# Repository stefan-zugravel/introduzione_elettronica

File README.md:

# Corso introduttivo "Flusso di progettazione elettronica"
Il corso prevede 4 ore di lezione frontale e diversi laboratori da svolgere in autonomia.
Per scaricare sulla propria workstation tutto il materiale:
`git clone https://github.com/stefan-zugravel/introduzione_elettronica.git`
oppure:
`git clone git@github.com:stefan-zugravel/introduzione_elettronica.git`
in base a proprio metodo di autenticazione preferito (consiglio chiave ssh)
**Se non avete mai uasto GIT vi consiglio di guardare uno di due video prima del corso**
- [video 1](https://www.youtube.com/watch?v=8JJ101D3knE)
- [video 2](https://www.youtube.com/watch?v=tRZGeaHPoaw)
***
## Lezione online sincrona
Dato il limitato tempo a disposizione la lezione sicrona si dovrà concentrare maggiormente sull'aspetto teorico e su ebventuali consigli pratici. Cercheremo comunque di vedere assieme, per i due tool più importanti (KiCAD e VIVADO), come creare un nuoo progetto e quali sono le funzioni principali del tool.
- Istruzioni per accedere ai laboratori con le consegne e le soluzioni (15 min) 
- Introduzione pcb con slides (45 min circa)
- KiCAD, aggiungere componenti, come funziona il tool e qualche accorgimento (45 min)
- Informazioni più generali sul workflow, BOM, produzione, materiali ecc (15 min)
- Pausa 10 min
- VHDL e FPGA introduzione con slides (60 min)
- VIVADO, introduzione al tool e strumenti principali (fino a termine lezione)
***
## Laboratori
### Lab 0 - Laboratorio introduttivo su GIT
**Consegna:** Crea una nuova *repo* su GitHub con un gitignore, una licenza e un README. Fai il *push* di un *commit*, crea una o più nuove *branch* e fanne il merge.
Per prendere dimestichezza con il tool consiglio di creare una *repo* diversa per ogni nuovo laboratorio.
### Lab 1 - Tastierino in KiCAD
**Consegna:** In KiCAD realizza lo schematico, il layout e i file di produzione per un tastierino da 16 pulsanti. Questo laboratorio verrà svolto durante la lezione come introduzione al software.
### Lab 2 - Skew e length tuning in KiCAD
**Consegna:** Crea un nuovo progetto, importa due coppie di connettori coassiali a due poli (esempio: LEMO-EPG.00.302.NLN) e prendi dimestichezza con i tool di de-skewing e length tuning per le coppie differenziali e single ended. Sulle slides puoi trovare i link a due brevi video tutorial.
### Lab 3 - Amperometro in KiCAD
**Consegna:** Progetta (diagramma a blocchi, schematico, layout e file di produzione) un amperometro con le seguenti specifiche:
- 8 canali in ingresso
- Range di misurazione da 5 uA a 700 uA
- Risoluzione 16 bit
- Frequenza di campionamento di almeno 100 Sps
- FEE isolato galvanicamnete dalla parte digitale
- Filtro passa basso prima della digitalizzazione di 20 KHz -3 dB
- Invio dei dati ad un PC tramite ethernet TCP-IP

**Domande da porsi:**
- Devo usare un microcontrollore o un FPGA? Perché? Quali sono i benefit di uno e dell'altro?
- Come faccio a portare il power al FEE mantenendo l'isolazione galvanica?
- Cosa uso per implementare il protocollo ethernet TCP-IP in maniera semplice, veloce ed economica?
- Come posso misurare delle correnti così piccole? Che componenti devo usare?

**Consiglio:** 
- Controllate questo [modulo](https://docs.wiznet.io/Product/Chip/MCU/W55RP20/w55rp20-evb-pico), può esservi utile?

**Raccomandazioni:**
- Cercate di usare il meno possibile le soluzioni. Soprattutto per questo laboratorio. La parte più difficile del design molte volte è proprio all'inizio, scegliere l'architettura, il tipo di circuito da usare e su quali componenti fare affidamento. Ho volutamente omesso dai consigli tutti gli altri componenti da usare. Fate le vostre scelte e poi confrontatevi con la soluzione proposta (che non è detto essere la migliore).

### Lab 4 - FPGA e KiCAD
**Consegna:** Importa un FPGA a scelta in KiCAD, collega il power e qualche linea dati e prova a farne il layout. Questo laboratorio è il più _"difficile"_ in quanto le tolleranze in gioco sono generalmente piccole e la soluizone mostra solo un esempio di un layout finito e non un effettivo punto di arrivo del laboratorio. Sulle slides puoi trovare i link a due brevi video tutorial. Prendi il tempo necessario e **leggi la documentazione** dell'FPGA che hai scelto.
### Lab 5 - Introduzione a LTspice
**Consegna:** Con LTspice disegna lo schematico ed esegui la simulazione dei seguenti circuiti analogici:
- Un semplice partitore resistivo (simulazione .op e un .dc sweep)
- Amplificatore operazionale in configurazione non invertente (simulazione .ac e .tran)
- Amplificatore operazionale in configurazione invertente (simulazione .ac e .tran)
- Caratterizzazione di un MOSFET (che tipo di simulazione conviene usare?)
- Amplificatore operazionale importando una libreria esterna (il file .LIB è presente nella cartella del lab5)
- Amplificatore operazionale con feedback capacitivo (simulazione .ac e .tran)

**Consiglio di ripetere tutti i circuiti fatti su LTspice usando il simulatore integrato in KiCAD (ngspice).**

### Lab 6
**Consegna:** Usando VIVADO scrivi in VHDL i moduli per un inverter, per le porte logiche AND, OR, NAND, NOR, XOR, XNOR e il modulo per un multiplexer (questo può essere fatto in più varianti). Questo laboratorio verrà svolto durante la lezione come introduzione al software, vedremo inoltre il concetto di testbench, di sintesi e implementazione, il file di constraints e la generazione del bitfile.

### Lab 7
**Consegna:** Scivi in VHDL un BCD (Contatore Decimale condificato in Binario):
- Come posso variare la sua velocità di aggiornamento?
- Quanto lento lo posso far andare? E invece quanto veloce?
- Come posso configure la sua velocità nel modo più efficiente possibile?

### Lab 8
**Consegna:** Scrivi in VHDL una macchina a stati per il controllo dei semafori in un incrocio stradale. La parte importante di questo laboratorio è tutta la sintassi della macchina a stati finiti (FSM). In questo caso consiglio di guardare le soluzioni, prendere spunto e aggiungere uno stato di _allarme_ e uno di _inizializzazione_.

### Lab 9
**Consegna:** Usa il block diagram di VIVADO per implementare un FIR passa basso digitale usando due DDS compiler, un modulo di somma e una ILA. Il modulo del FIR puoi prenderlo dalla soluzioni. Cerca però di comprenderne il funzionamento. Consiglio di provare a modificarlo aumentando il numero di taps.

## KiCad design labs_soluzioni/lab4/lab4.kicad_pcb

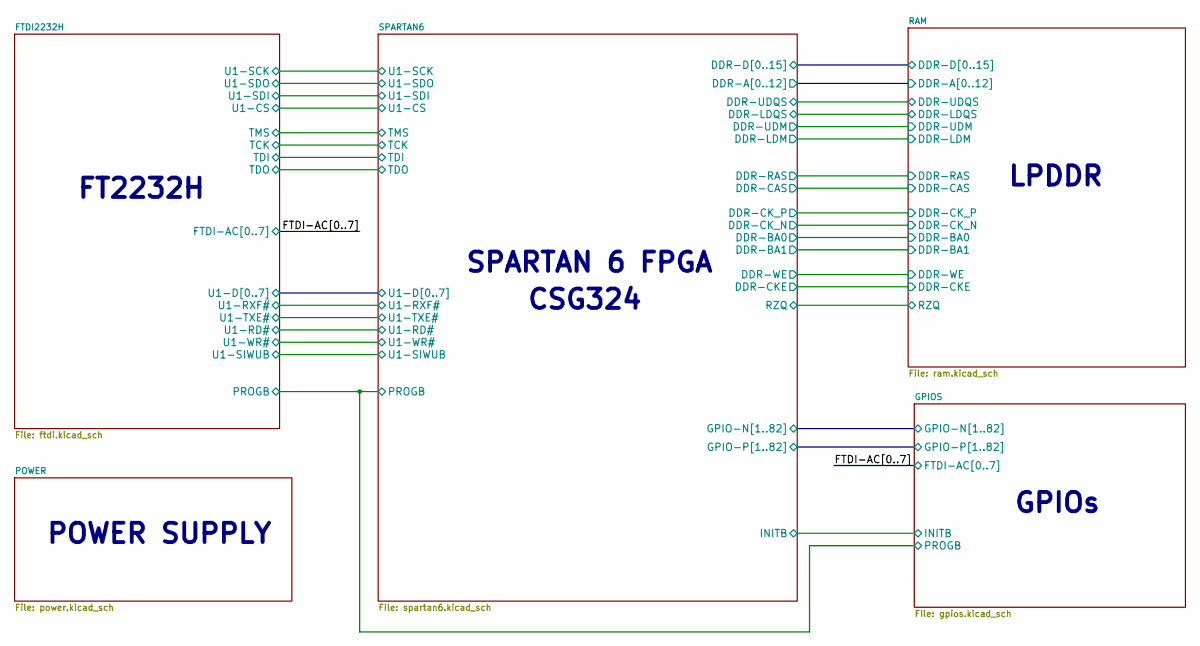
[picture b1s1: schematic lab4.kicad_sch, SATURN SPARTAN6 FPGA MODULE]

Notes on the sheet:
FT2232H
SPARTAN 6 FPGA
CSG324
GPIOs
LPDDR
POWER SUPPLY

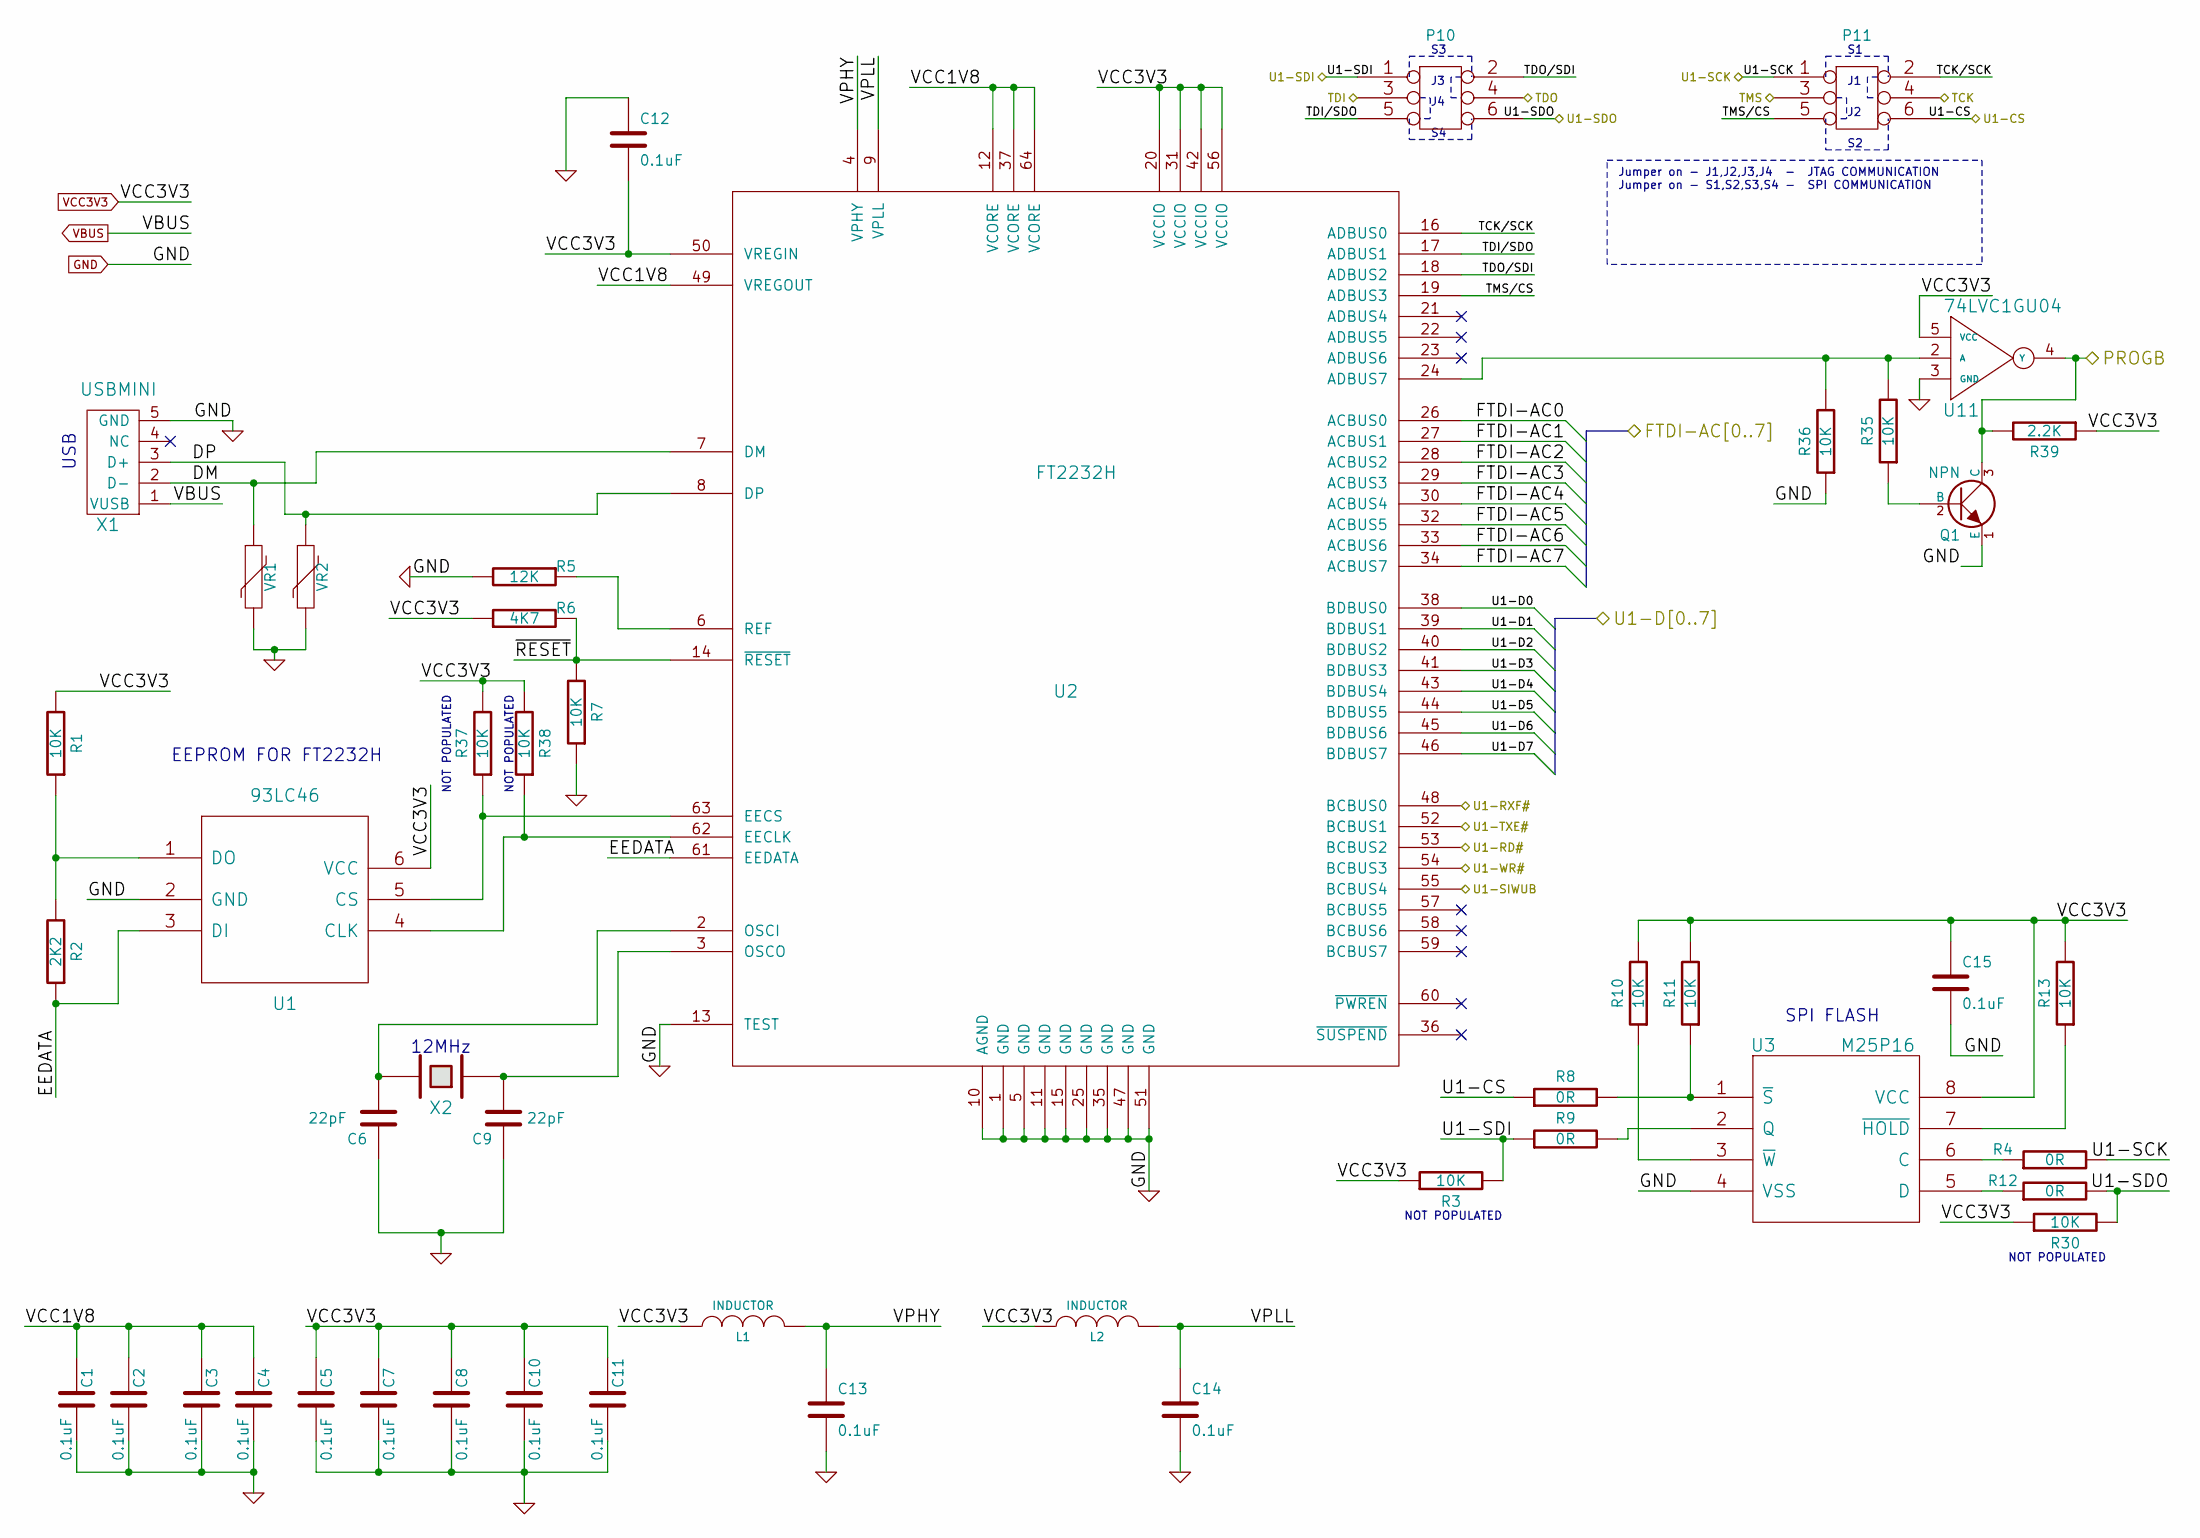
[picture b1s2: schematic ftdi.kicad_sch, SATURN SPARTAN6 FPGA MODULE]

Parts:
C1, C2, C3, C4, C5, C7, C8, C10, C11, C12, C13, C14, C15: 0.1uF
C6, C9: 22pF
L1, L2: INDUCTOR
P10, P11: CONN_3X2
Q1: NPN
R1, R3, R7, R10, R11, R13, R30, R35, R36, R37, R38: 10K
R2: 2K2
R4, R8, R9, R12: 0R
R5: 12K
R6: 4K7
R39: 2.2K
U1: 93LC46
U2: FT2232H
U3: M25P16
U11: 74LVC1GU04
VR1, VR2: VR
X1: USBMINI
X2: CRYSTAL

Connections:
/FTDI2232H/DM: U2.7 (DM), VR1.1, X1.2 (D-)
/FTDI2232H/DP: U2.8 (DP), VR2.1, X1.3 (D+)
/FTDI2232H/EEDATA: R2.1, U1.3 (DI), U2.61 (EEDATA)
/FTDI2232H/FTDI-AC0: U2.26 (ACBUS0); also elsewhere on the board
/FTDI2232H/FTDI-AC1: U2.27 (ACBUS1); also elsewhere on the board
/FTDI2232H/FTDI-AC2: U2.28 (ACBUS2); also elsewhere on the board
/FTDI2232H/FTDI-AC3: U2.29 (ACBUS3); also elsewhere on the board
/FTDI2232H/FTDI-AC4: U2.30 (ACBUS4); also elsewhere on the board
/FTDI2232H/FTDI-AC5: U2.32 (ACBUS5); also elsewhere on the board
/FTDI2232H/FTDI-AC6: U2.33 (ACBUS6); also elsewhere on the board
/FTDI2232H/FTDI-AC7: U2.34 (ACBUS7); also elsewhere on the board
/FTDI2232H/PROGB: Q1.3 (C), R39.2, U11.4 (Y); also elsewhere on the board
/FTDI2232H/TCK: P11.4; also elsewhere on the board
/FTDI2232H/TCK/SCK: P11.2, U2.16 (ADBUS0)
/FTDI2232H/TDI: P10.3; also elsewhere on the board
/FTDI2232H/TDI/SDO: P10.5, U2.17 (ADBUS1)
/FTDI2232H/TDO: P10.4; also elsewhere on the board
/FTDI2232H/TDO/SDI: P10.2, U2.18 (ADBUS2)
/FTDI2232H/TMS: P11.3; also elsewhere on the board
/FTDI2232H/TMS/CS: P11.5, U2.19 (ADBUS3)
/FTDI2232H/U1-CS: P11.6, R8.1; also elsewhere on the board
/FTDI2232H/U1-D0: U2.38 (BDBUS0); also elsewhere on the board
/FTDI2232H/U1-D1: U2.39 (BDBUS1); also elsewhere on the board
/FTDI2232H/U1-D2: U2.40 (BDBUS2); also elsewhere on the board
/FTDI2232H/U1-D3: U2.41 (BDBUS3); also elsewhere on the board
/FTDI2232H/U1-D4: U2.43 (BDBUS4); also elsewhere on the board
/FTDI2232H/U1-D5: U2.44 (BDBUS5); also elsewhere on the board
/FTDI2232H/U1-D6: U2.45 (BDBUS6); also elsewhere on the board
/FTDI2232H/U1-D7: U2.46 (BDBUS7); also elsewhere on the board
/FTDI2232H/U1-RD#: U2.53 (BCBUS2); also elsewhere on the board
/FTDI2232H/U1-RXF#: U2.48 (BCBUS0); also elsewhere on the board
/FTDI2232H/U1-SCK: P11.1, R4.2; also elsewhere on the board
/FTDI2232H/U1-SDI: P10.1, R3.2, R9.1; also elsewhere on the board
/FTDI2232H/U1-SDO: P10.6, R12.2, R30.2; also elsewhere on the board
/FTDI2232H/U1-SIWUB: U2.55 (BCBUS4); also elsewhere on the board
/FTDI2232H/U1-TXE#: U2.52 (BCBUS1); also elsewhere on the board
/FTDI2232H/U1-WR#: U2.54 (BCBUS3); also elsewhere on the board
/FTDI2232H/VCC1V8: C1.1, C2.1, C3.1, C4.1, U2.12 (VCORE), U2.37 (VCORE), U2.49 (VREGOUT), U2.64 (VCORE)
/FTDI2232H/VPHY: C13.1, L1.2, U2.4 (VPHY)
/FTDI2232H/VPLL: C14.1, L2.2, U2.9 (VPLL)
/FTDI2232H/~RESET: R6.2, R7.2, U2.14 (~RESET)
GND: C1.2, C2.2, C3.2, C4.2, C5.2, C6.1, C7.2, C8.2, C9.1, C10.2, C11.2, C12.1, C13.2, C14.2, C15.2, Q1.1 (E), R5.2, R7.1, R36.1, U1.2 (GND), U2.1 (GND), U2.5 (GND), U2.10 (AGND), U2.11 (GND), U2.13 (TEST), U2.15 (GND), U2.25 (GND), U2.35 (GND), U2.47 (GND), U2.51 (GND), U3.4 (VSS), U11.3 (GND), VR1.2, VR2.2, X1.0, X1.5 (GND); also elsewhere on the board
unnamed: R13.1, U3.7 (~HOLD)
unnamed: R9.2, U3.2 (Q)
unnamed: R12.1, U3.5 (D)
unnamed: R8.2, R11.1, U3.1 (~S)
unnamed: R10.1, U3.3 (~W)
unnamed: R4.1, U3.6 (C)
unnamed: R35.2, R36.2, U2.24 (ADBUS7), U11.2 (A)
unnamed: C9.2, U2.3 (OSCO), X2.1
unnamed: R37.1, U1.5 (CS), U2.63 (EECS)
unnamed: R1.1, R2.2, U1.1 (DO)
unnamed: C6.2, U2.2 (OSCI), X2.2
unnamed: Q1.2 (B), R35.1
unnamed: R38.1, U1.4 (CLK), U2.62 (EECLK)
unnamed: R5.1, U2.6 (REF)
VBUS: X1.1 (VUSB); also elsewhere on the board
VCC3V3: C5.1, C7.1, C8.1, C10.1, C11.1, C12.2, C15.1, L1.1, L2.1, R1.2, R3.1, R6.1, R10.2, R11.2, R13.2, R30.1, R37.2, R38.2, R39.1, U1.6 (VCC), U2.20 (VCCIO), U2.31 (VCCIO), U2.42 (VCCIO), U2.50 (VREGIN), U2.56 (VCCIO), U3.8 (VCC), U11.5 (VCC); also elsewhere on the board

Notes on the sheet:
NOT POPULATED
12MHz
EEPROM FOR FT2232H
SPI FLASH
USB
Jumper on - J1,J2,J3,J4 - JTAG COMMUNICATION Jumper on - S1,S2,S3,S4 - SPI COMMUNICATION

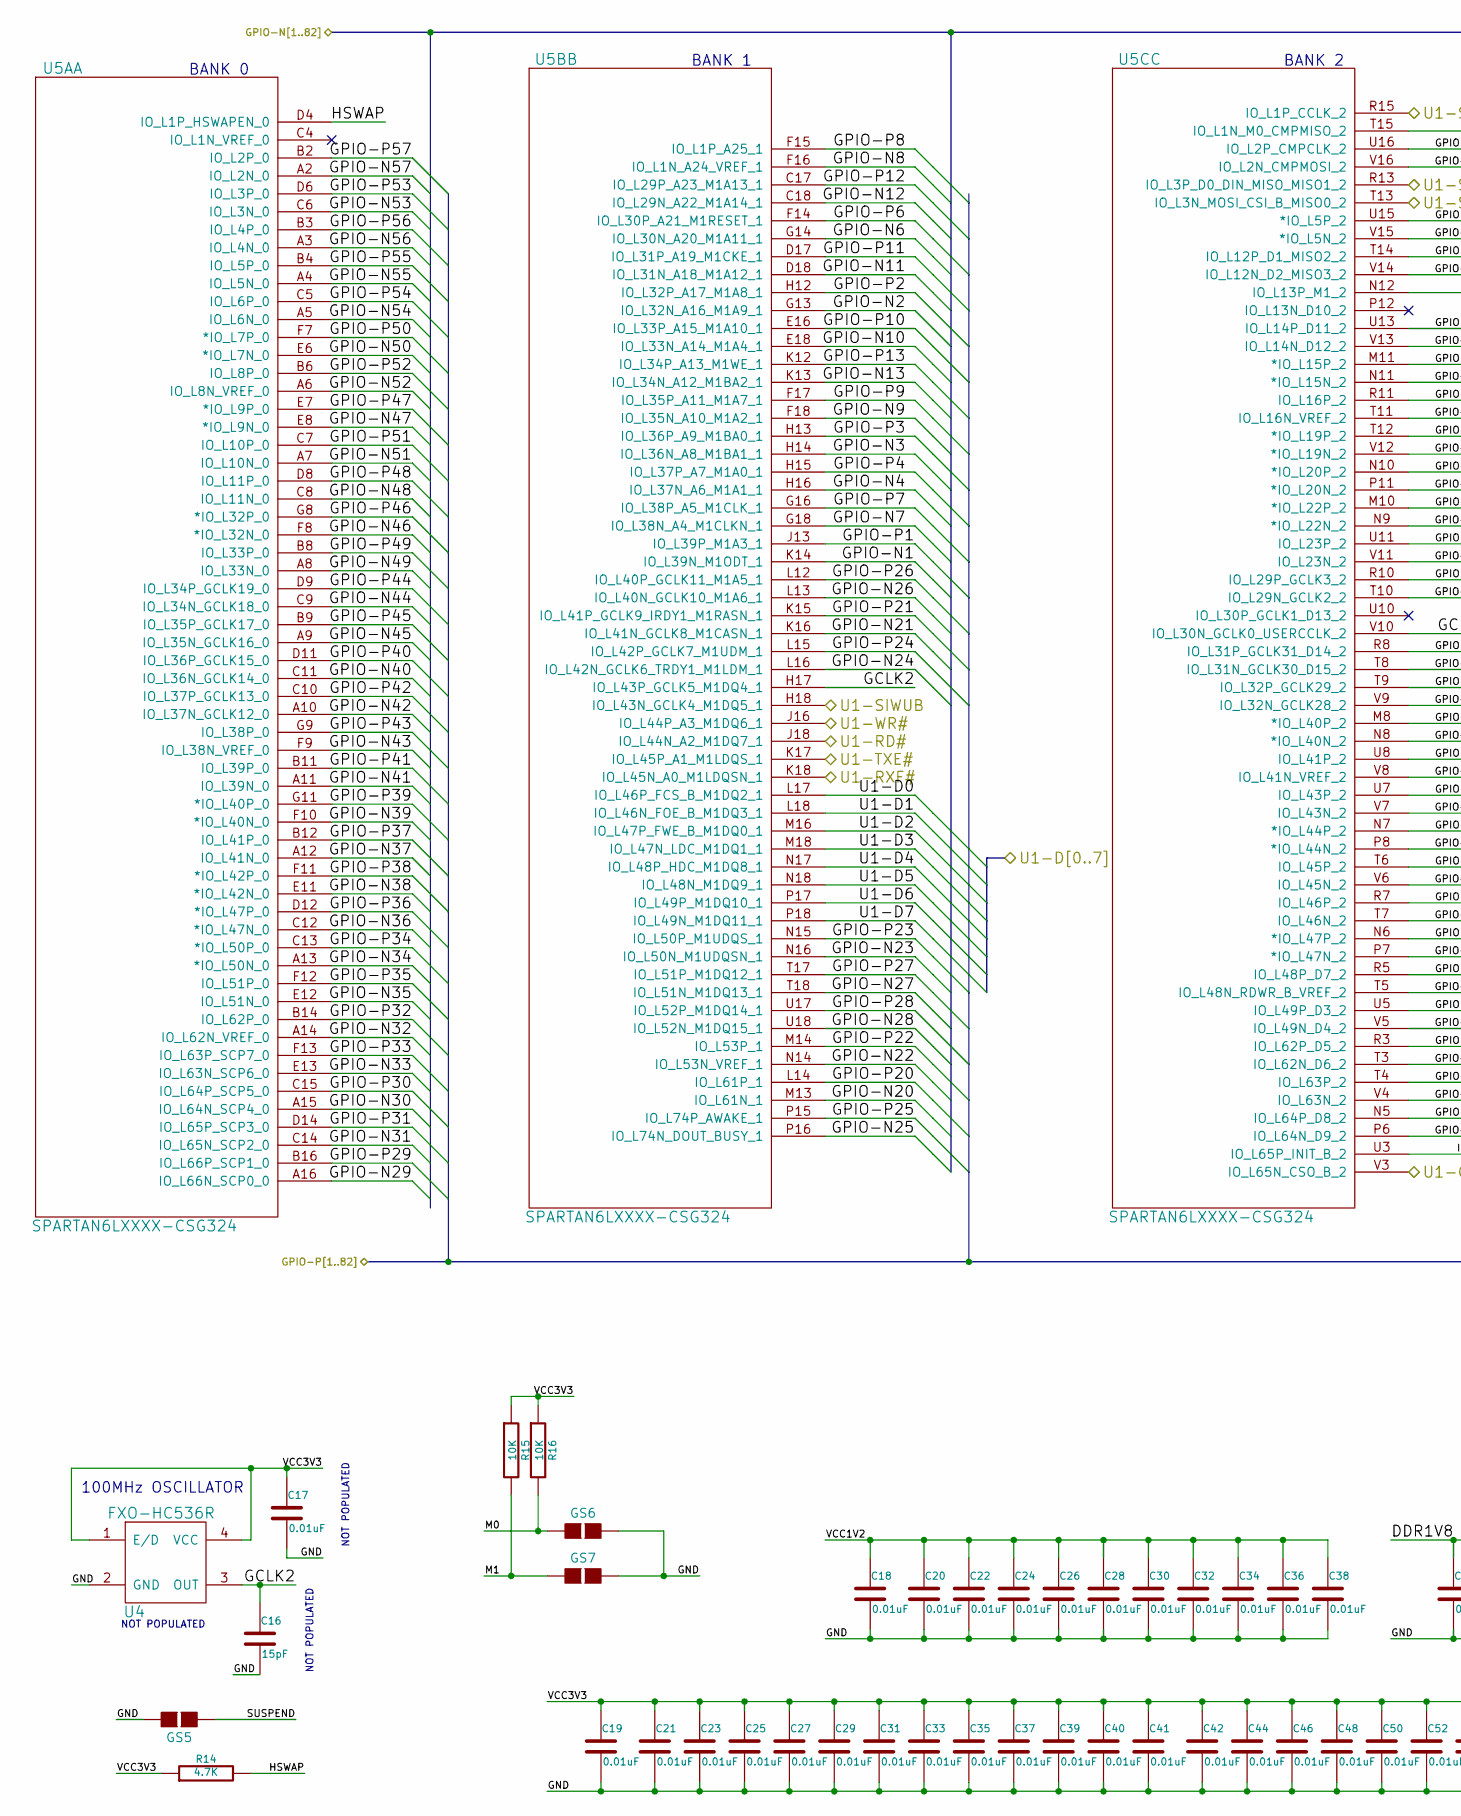
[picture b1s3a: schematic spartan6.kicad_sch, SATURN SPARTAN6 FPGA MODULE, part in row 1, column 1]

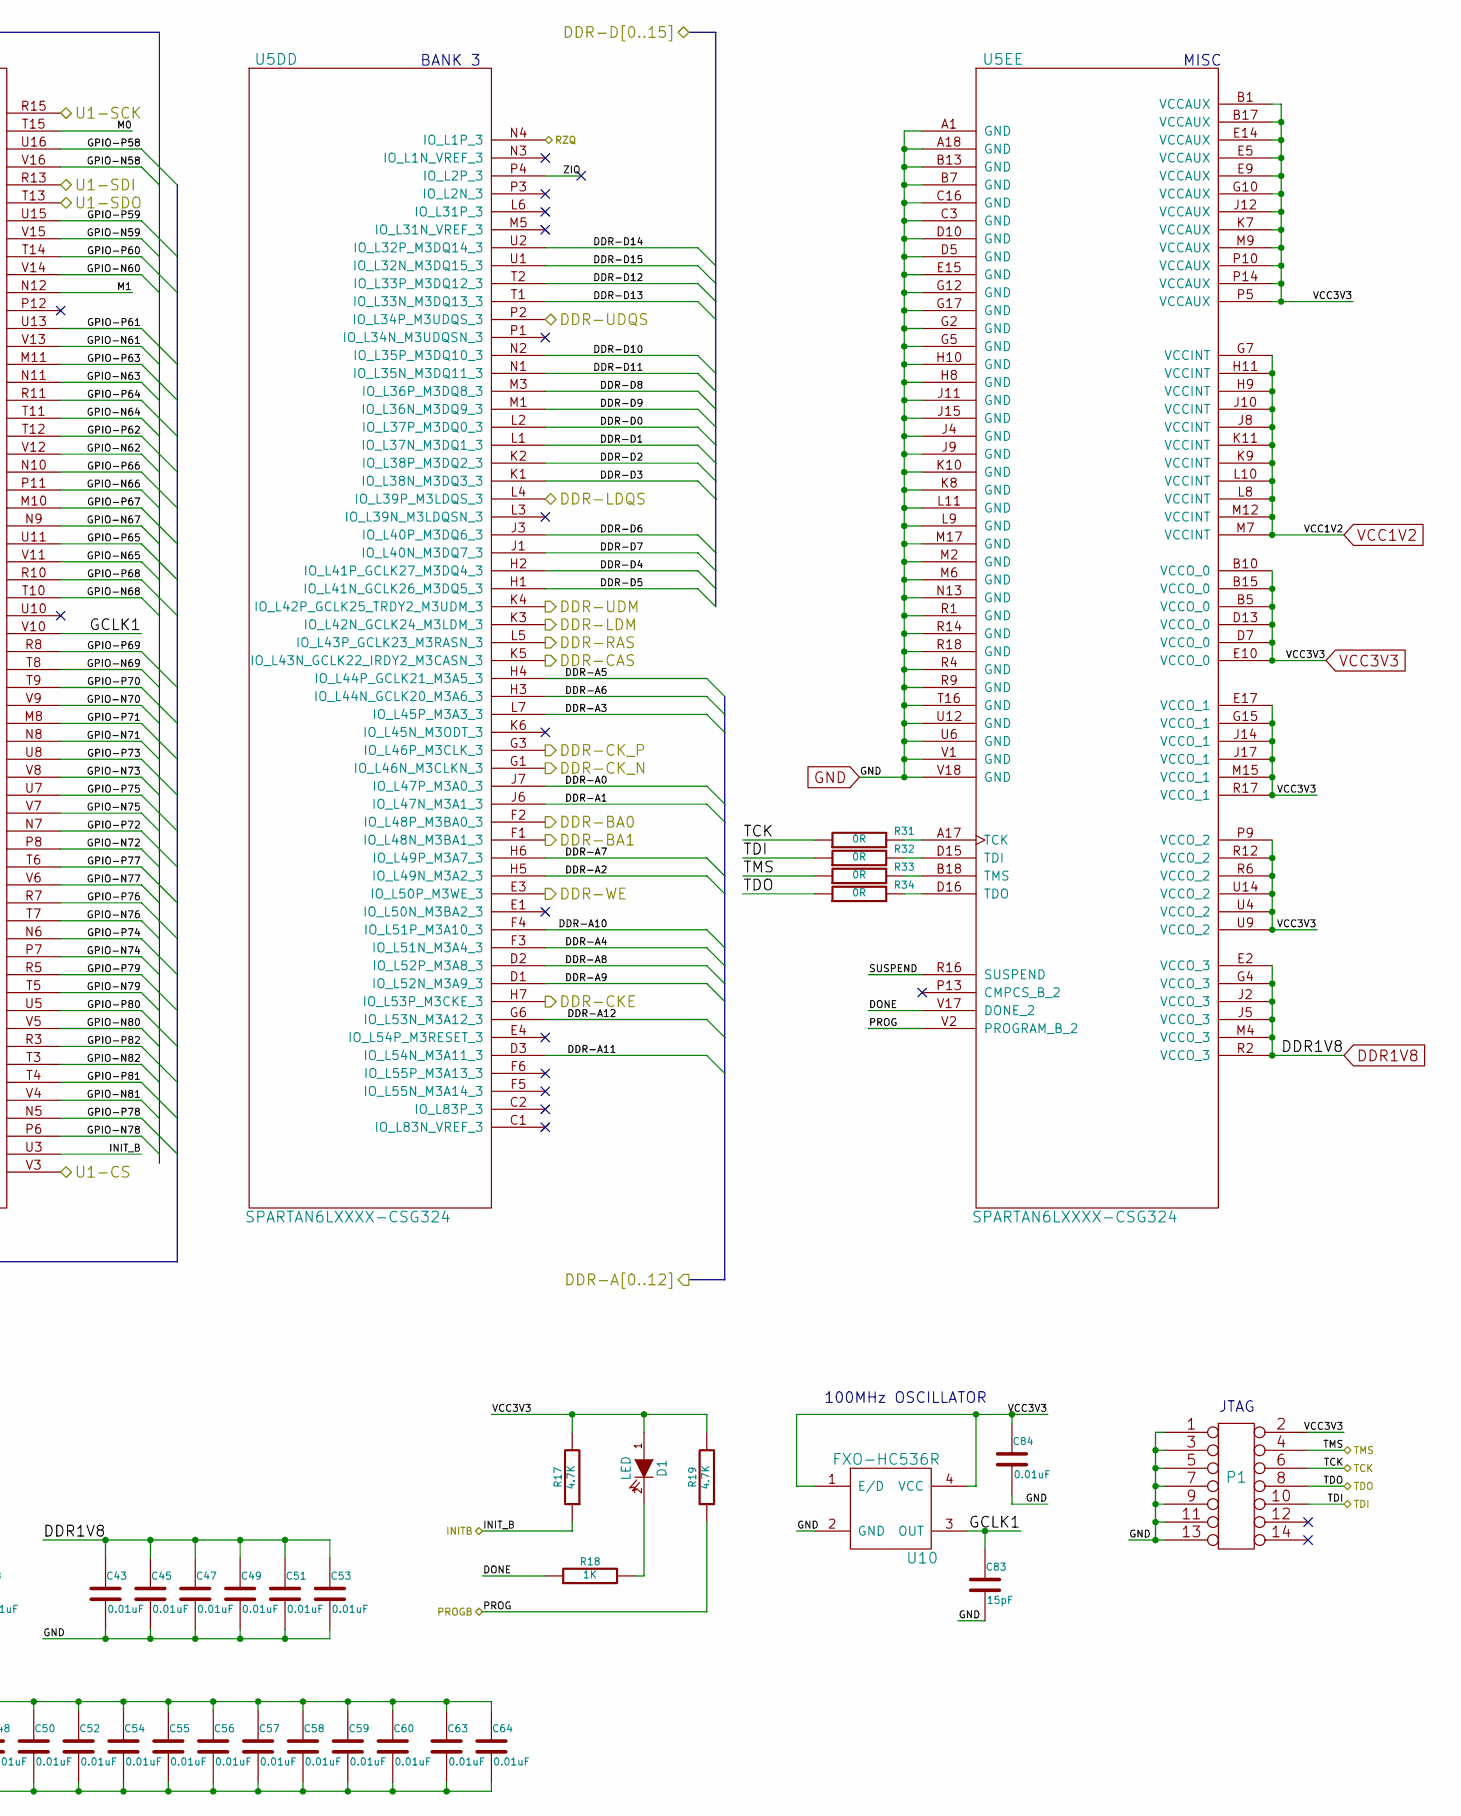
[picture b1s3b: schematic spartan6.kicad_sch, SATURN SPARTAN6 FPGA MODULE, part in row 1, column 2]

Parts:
C16, C83: 15pF
C17, C18, C19, C20, C21, C22, C23, C24, C25, C26, C27, C28, C29, C30, C31, C32, C33, C34, C35, C36, C37, C38, C39, C40, C41, C42, C43, C44, C45, C46, C47, C48, C49, C50, C51, C52, C53, C54, C55, C56, C57, C58, C59, C60, C63, C64, C84: 0.01uF
D1: LED
GS5, GS6, GS7: GS2
P1: CONN_7X2
R14, R17, R19: 4.7K
R15, R16: 10K
R18: 1K
R31, R32, R33, R34: 0R
U4, U10: FXO-HC536R
U5A, U5B, U5C, U5D, U5E: SPARTAN6LXXXX-CSG324

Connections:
/FTDI2232H/PROGB: R19.1, U5E.V2 (PROGRAM_B_2); also elsewhere on the board
/FTDI2232H/TCK: P1.6, R31.1; also elsewhere on the board
/FTDI2232H/TDI: P1.10, R32.1; also elsewhere on the board
/FTDI2232H/TDO: P1.8, R34.1; also elsewhere on the board
/FTDI2232H/TMS: P1.4, R33.1; also elsewhere on the board
/GPIOS/INITB: R17.1, U5C.U3 (IO_L65P_INIT_B_2); also elsewhere on the board
/SPARTAN6/DONE: R18.1, U5E.V17 (DONE_2); also elsewhere on the board
/SPARTAN6/GCLK1: C83.1, U5C.V10 (IO_L30N_GCLK0_USERCCLK_2), U10.3 (OUT); also elsewhere on the board
/SPARTAN6/GCLK2: C16.1, U4.3 (OUT), U5B.H17 (IO_L43P_GCLK5_M1DQ4_1); also elsewhere on the board
/SPARTAN6/HSWAP: R14.2, U5A.D4 (IO_L1P_HSWAPEN_0); also elsewhere on the board
/SPARTAN6/M0: GS6.1 (G1), R16.2, U5C.T15 (IO_L1N_M0_CMPMISO_2); also elsewhere on the board
/SPARTAN6/M1: GS7.1 (G1), R15.2, U5C.N12 (IO_L13P_M1_2); also elsewhere on the board
/SPARTAN6/SUSPEND: GS5.1 (G1), U5E.R16 (SUSPEND); also elsewhere on the board
DDR1V8: C43.1, C45.1, C47.1, C49.1, C51.1, C53.1, U5E.E2 (VCCO_3), U5E.G4 (VCCO_3), U5E.J2 (VCCO_3), U5E.J5 (VCCO_3), U5E.M4 (VCCO_3), U5E.R2 (VCCO_3); also elsewhere on the board
GND: C16.2, C17.2, C18.2, C19.2, C20.2, C21.2, C22.2, C23.2, C24.2, C25.2, C26.2, C27.2, C28.2, C29.2, C30.2, C31.2, C32.2, C33.2, C34.2, C35.2, C36.2, C37.2, C38.2, C39.2, C40.2, C41.2, C42.2, C43.2, C44.2, C45.2, C46.2, C47.2, C48.2, C49.2, C50.2, C51.2, C52.2, C53.2, C54.2, C55.2, C56.2, C57.2, C58.2, C59.2, C60.2, C63.2, C64.2, C83.2, C84.2, GS5.2 (G2), GS6.2 (G2), GS7.2 (G2), P1.1, P1.3, P1.5, P1.7, P1.9, P1.11, P1.13, U4.2 (GND), U5E.A1 (GND), U5E.A18 (GND), U5E.B7 (GND), U5E.B13 (GND), U5E.C3 (GND), U5E.C16 (GND), U5E.D5 (GND), U5E.D10 (GND), U5E.E15 (GND), U5E.G2 (GND), U5E.G5 (GND), U5E.G12 (GND), U5E.G17 (GND), U5E.H8 (GND), U5E.H10 (GND), U5E.J4 (GND), U5E.J9 (GND), U5E.J11 (GND), U5E.J15 (GND), U5E.K8 (GND), U5E.K10 (GND), U5E.L9 (GND), U5E.L11 (GND), U5E.M2 (GND), U5E.M6 (GND), U5E.M17 (GND), U5E.N13 (GND), U5E.R1 (GND), U5E.R4 (GND), U5E.R9 (GND), U5E.R14 (GND), U5E.R18 (GND), U5E.T16 (GND), U5E.U6 (GND), U5E.U12 (GND), U5E.V1 (GND), U5E.V18 (GND), U10.2 (GND); also elsewhere on the board
unnamed 257: R31.2, U5E.A17 (TCK); also elsewhere on the board
unnamed 258: R34.2, U5E.D16 (TDO); also elsewhere on the board
unnamed 259: R32.2, U5E.D15 (TDI); also elsewhere on the board
unnamed 260: R33.2, U5E.B18 (TMS); also elsewhere on the board
unnamed: D1.2 (K), R18.2
VCC1V2: C18.1, C20.1, C22.1, C24.1, C26.1, C28.1, C30.1, C32.1, C34.1, C36.1, C38.1, U5E.G7 (VCCINT), U5E.H9 (VCCINT), U5E.H11 (VCCINT), U5E.J8 (VCCINT), U5E.J10 (VCCINT), U5E.K9 (VCCINT), U5E.K11 (VCCINT), U5E.L8 (VCCINT), U5E.L10 (VCCINT), U5E.M7 (VCCINT), U5E.M12 (VCCINT); also elsewhere on the board
VCC3V3: C17.1, C19.1, C21.1, C23.1, C25.1, C27.1, C29.1, C31.1, C33.1, C35.1, C37.1, C39.1, C40.1, C41.1, C42.1, C44.1, C46.1, C48.1, C50.1, C52.1, C54.1, C55.1, C56.1, C57.1, C58.1, C59.1, C60.1, C63.1, C64.1, C84.1, D1.1 (A), P1.2, R14.1, R15.1, R16.1, R17.2, R19.2, U4.1 (E/D), U4.4 (VCC), U5E.B1 (VCCAUX), U5E.B5 (VCCO_0), U5E.B10 (VCCO_0), U5E.B15 (VCCO_0), U5E.B17 (VCCAUX), U5E.D7 (VCCO_0), U5E.D13 (VCCO_0), U5E.E5 (VCCAUX), U5E.E9 (VCCAUX), U5E.E10 (VCCO_0), U5E.E14 (VCCAUX), U5E.E17 (VCCO_1), U5E.G10 (VCCAUX), U5E.G15 (VCCO_1), U5E.J12 (VCCAUX), U5E.J14 (VCCO_1), U5E.J17 (VCCO_1), U5E.K7 (VCCAUX), U5E.M9 (VCCAUX), U5E.M15 (VCCO_1), U5E.P5 (VCCAUX), U5E.P9 (VCCO_2), U5E.P10 (VCCAUX), U5E.P14 (VCCAUX), U5E.R6 (VCCO_2), U5E.R12 (VCCO_2), U5E.R17 (VCCO_1), U5E.U4 (VCCO_2), U5E.U9 (VCCO_2), U5E.U14 (VCCO_2), U10.1 (E/D), U10.4 (VCC); also elsewhere on the board

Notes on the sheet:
100MHz OSCILLATOR
BANK 3
BANK 2
NOT POPULATED
JTAG
BANK 1
MISC
BANK 0

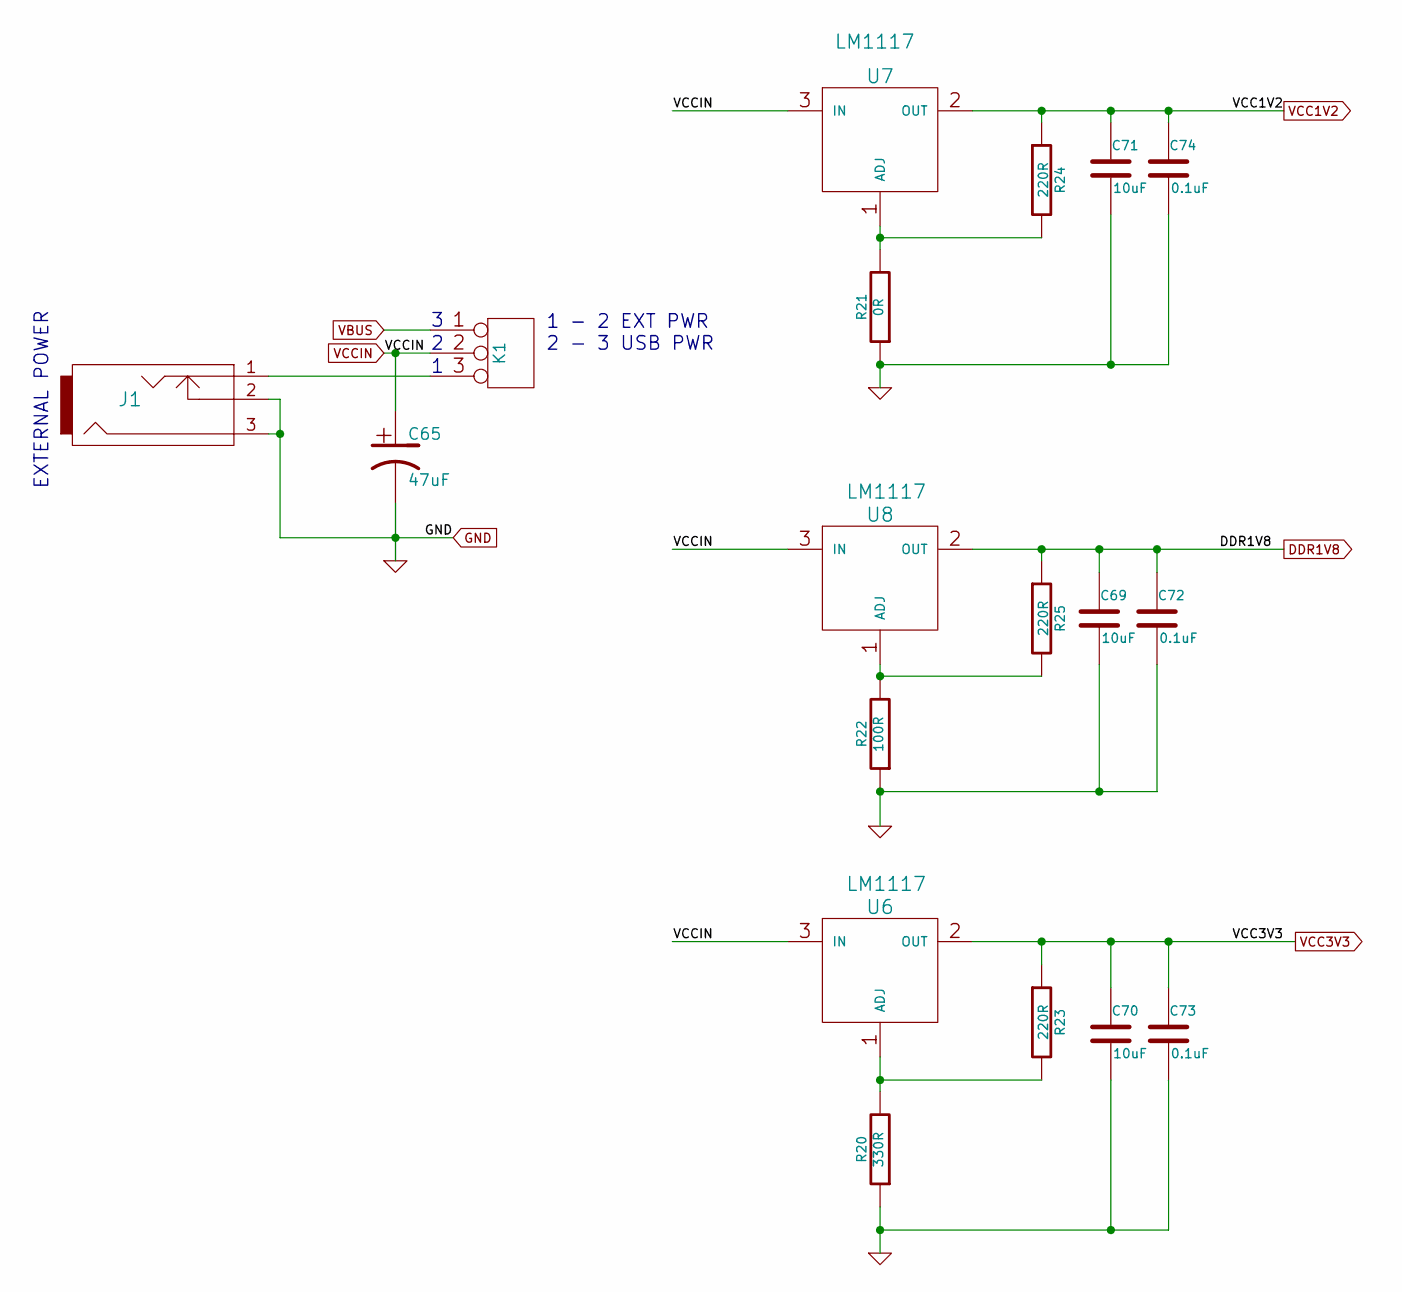
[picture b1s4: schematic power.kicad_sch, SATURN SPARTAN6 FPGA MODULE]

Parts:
C65: 47uF
C69, C70, C71: 10uF
C72, C73, C74: 0.1uF
J1: JACK_2P
K1: CONN_3
R20: 330R
R21: 0R
R22: 100R
R23, R24, R25: 220R
U6, U7, U8: LM1117

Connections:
DDR1V8: C69.1, C72.1, R25.1, U8.2 (OUT); also elsewhere on the board
GND: C65.2, C69.2, C70.2, C71.2, C72.2, C73.2, C74.2, J1.2, J1.3, R20.1, R21.1, R22.1; also elsewhere on the board
unnamed: R20.2, R23.2, U6.1 (ADJ)
unnamed: R21.2, R24.2, U7.1 (ADJ)
unnamed: R22.2, R25.2, U8.1 (ADJ)
unnamed: J1.1, K1.3
VBUS: K1.1; also elsewhere on the board
VCC1V2: C71.1, C74.1, R24.1, U7.2 (OUT); also elsewhere on the board
VCC3V3: C70.1, C73.1, R23.1, U6.2 (OUT); also elsewhere on the board
VCCIN: C65.1, K1.2 (PM), U6.3 (IN), U7.3 (IN), U8.3 (IN); also elsewhere on the board

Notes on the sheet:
EXTERNAL POWER
1 - 2 EXT PWR 2 - 3 USB PWR

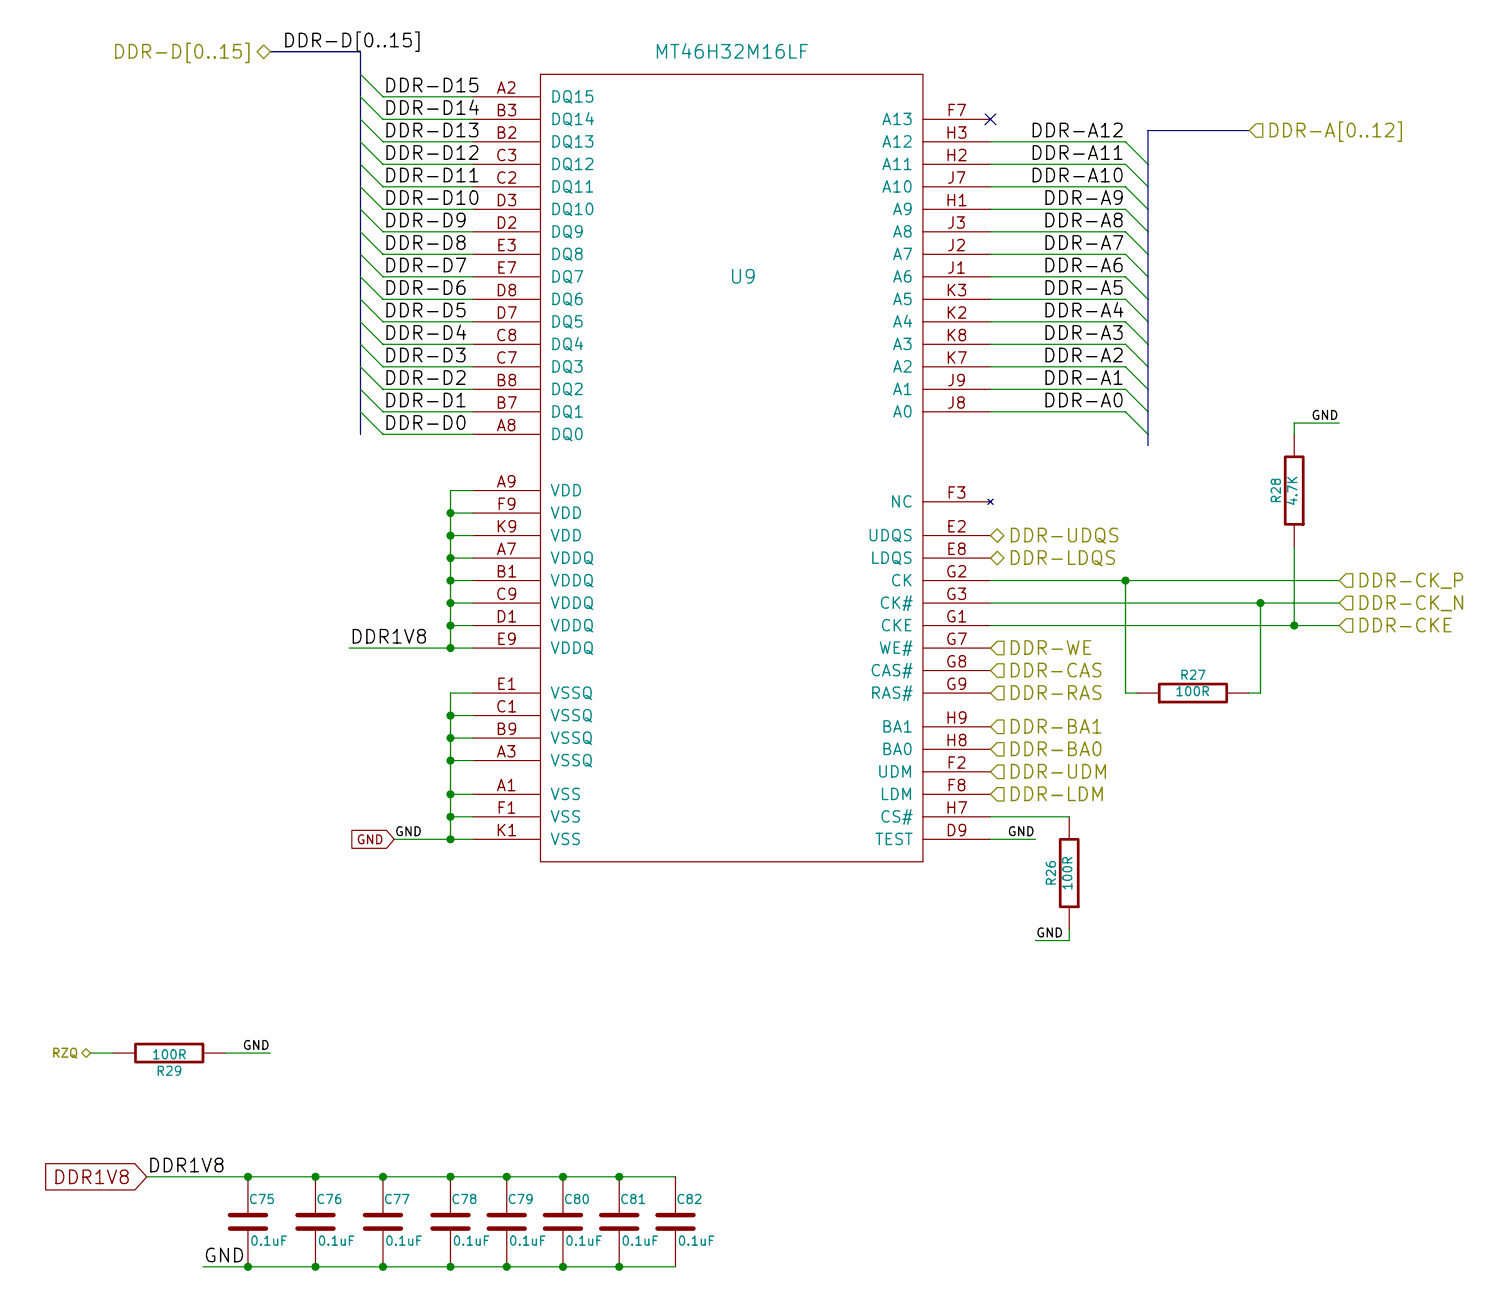
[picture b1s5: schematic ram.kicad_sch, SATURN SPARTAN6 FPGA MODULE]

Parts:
C75, C76, C77, C78, C79, C80, C81, C82: 0.1uF
R26, R27, R29: 100R
R28: 4.7K
U9: MT46H32M16LF

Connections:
/RAM/DDR-A0: U9.J8 (A0); also elsewhere on the board
/RAM/DDR-A1: U9.J9 (A1); also elsewhere on the board
/RAM/DDR-A2: U9.K7 (A2); also elsewhere on the board
/RAM/DDR-A3: U9.K8 (A3); also elsewhere on the board
/RAM/DDR-A4: U9.K2 (A4); also elsewhere on the board
/RAM/DDR-A5: U9.K3 (A5); also elsewhere on the board
/RAM/DDR-A6: U9.J1 (A6); also elsewhere on the board
/RAM/DDR-A7: U9.J2 (A7); also elsewhere on the board
/RAM/DDR-A8: U9.J3 (A8); also elsewhere on the board
/RAM/DDR-A9: U9.H1 (A9); also elsewhere on the board
/RAM/DDR-A10: U9.J7 (A10); also elsewhere on the board
/RAM/DDR-A11: U9.H2 (A11); also elsewhere on the board
/RAM/DDR-A12: U9.H3 (A12); also elsewhere on the board
/RAM/DDR-BA0: U9.H8 (BA0); also elsewhere on the board
/RAM/DDR-BA1: U9.H9 (BA1); also elsewhere on the board
/RAM/DDR-CAS: U9.G8 (CAS#); also elsewhere on the board
/RAM/DDR-CKE: R28.1, U9.G1 (CKE); also elsewhere on the board
/RAM/DDR-CK_N: R27.2, U9.G3 (CK#); also elsewhere on the board
/RAM/DDR-CK_P: R27.1, U9.G2 (CK); also elsewhere on the board
/RAM/DDR-D0: U9.A8 (DQ0); also elsewhere on the board
/RAM/DDR-D1: U9.B7 (DQ1); also elsewhere on the board
/RAM/DDR-D2: U9.B8 (DQ2); also elsewhere on the board
/RAM/DDR-D3: U9.C7 (DQ3); also elsewhere on the board
/RAM/DDR-D4: U9.C8 (DQ4); also elsewhere on the board
/RAM/DDR-D5: U9.D7 (DQ5); also elsewhere on the board
/RAM/DDR-D6: U9.D8 (DQ6); also elsewhere on the board
/RAM/DDR-D7: U9.E7 (DQ7); also elsewhere on the board
/RAM/DDR-D8: U9.E3 (DQ8); also elsewhere on the board
/RAM/DDR-D9: U9.D2 (DQ9); also elsewhere on the board
/RAM/DDR-D10: U9.D3 (DQ10); also elsewhere on the board
/RAM/DDR-D11: U9.C2 (DQ11); also elsewhere on the board
/RAM/DDR-D12: U9.C3 (DQ12); also elsewhere on the board
/RAM/DDR-D13: U9.B2 (DQ13); also elsewhere on the board
/RAM/DDR-D14: U9.B3 (DQ14); also elsewhere on the board
/RAM/DDR-D15: U9.A2 (DQ15); also elsewhere on the board
/RAM/DDR-LDM: U9.F8 (LDM); also elsewhere on the board
/RAM/DDR-LDQS: U9.E8 (LDQS); also elsewhere on the board
/RAM/DDR-RAS: U9.G9 (RAS#); also elsewhere on the board
/RAM/DDR-UDM: U9.F2 (UDM); also elsewhere on the board
/RAM/DDR-UDQS: U9.E2 (UDQS); also elsewhere on the board
/RAM/DDR-WE: U9.G7 (WE#); also elsewhere on the board
/RAM/RZQ: R29.2; also elsewhere on the board
DDR1V8: C75.1, C76.1, C77.1, C78.1, C79.1, C80.1, C81.1, C82.1, U9.A7 (VDDQ), U9.A9 (VDD), U9.B1 (VDDQ), U9.C9 (VDDQ), U9.D1 (VDDQ), U9.E9 (VDDQ), U9.F9 (VDD), U9.K9 (VDD); also elsewhere on the board
GND: C75.2, C76.2, C77.2, C78.2, C79.2, C80.2, C81.2, C82.2, R26.1, R28.2, R29.1, U9.A1 (VSS), U9.A3 (VSSQ), U9.B9 (VSSQ), U9.C1 (VSSQ), U9.D9 (TEST), U9.E1 (VSSQ), U9.F1 (VSS), U9.K1 (VSS); also elsewhere on the board
unnamed: R26.2, U9.H7 (CS#)

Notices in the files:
labs_soluzioni/lab4/ftdi.kicad_sch:
License: CC BY-SA
